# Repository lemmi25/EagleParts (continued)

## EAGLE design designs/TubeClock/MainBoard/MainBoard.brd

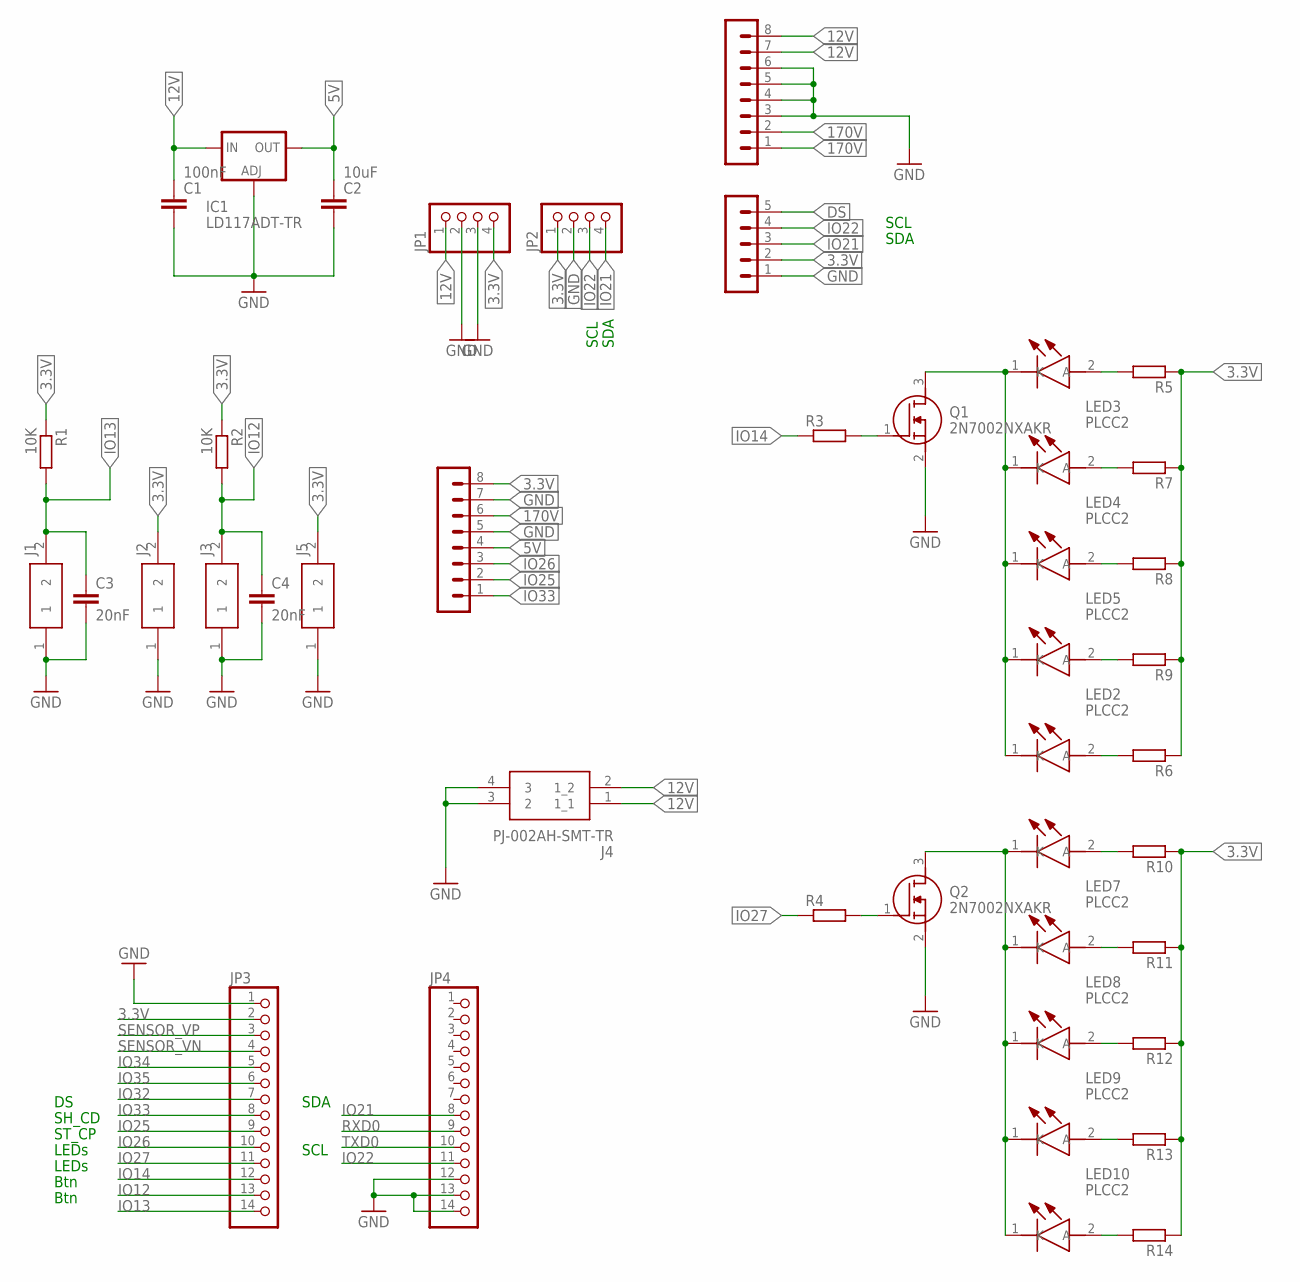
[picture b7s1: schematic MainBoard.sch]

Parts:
C1: 100nF; C1206
C2: 10uF; C1206
C3, C4: 20nF; C0805
IC1: LD117ADT-TR; DPACK
J1, J2, J3, J5: S2B-NSHSS-TB; SM02B-NSHSS-TB
J4: PJ-002AH-SMT-TR
JP1, JP2: PINHD-1X4; 1X04
JP3, JP4: PINHD-1X14; 1X14
LED1, LED2, LED3, LED4, LED5, LED6, LED7, LED8, LED9, LED10: PLCC2; LEDM3528X200N
Q1, Q2: 2N7002NXAKR; SOT95P230X110-3N
R1, R2: 10K; R1206
R3, R4, R5, R6, R7, R8, R9, R10, R11, R12, R13, R14: R-EU_1206R1206; R1206
SV1, SV7: PINHEADER-1X8; MA08-1
SV6: MA05-1

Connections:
3.3V: J2.2, J5.2, JP1.4, JP2.1, JP3.2, R1.1, R2.1, R5.1, R6.1, R7.1, R8.1, R9.1, R10.1, R11.1, R12.1, R13.1, R14.1, SV1.8, SV6.2
5V: C2.1, IC1.4 (OUT), SV1.4
12V: C1.1, IC1.3 (IN), J4.1 (1_1), J4.2 (1_2), JP1.1, SV7.7, SV7.8
170V: SV1.6, SV7.1, SV7.2
DS: SV6.5
GND: C1.2, C2.2, C3.2, C4.2, IC1.1 (ADJ), J1.1, J2.1, J3.1, J4.3 (2), J4.4 (3), J5.1, JP1.2, JP1.3, JP2.2, JP3.1, JP4.12, JP4.13, JP4.14, Q1.2 (S), Q2.2 (S), SV1.5, SV1.7, SV6.1, SV7.3, SV7.4, SV7.5, SV7.6
GND_LED_BTM: LED6.1 (K), LED7.1 (K), LED8.1 (K), LED9.1 (K), LED10.1 (K), Q2.3 (D)
GND_LED_TOP: LED1.1 (K), LED2.1 (K), LED3.1 (K), LED4.1 (K), LED5.1 (K), Q1.3 (D)
IO12: C4.1, J3.2, JP3.13, R2.2
IO13: C3.1, J1.2, JP3.14, R1.2
IO14: JP3.12, R3.1
IO21: JP2.4, JP4.8, SV6.3
IO22: JP2.3, JP4.11, SV6.4
IO25: JP3.9, SV1.2
IO26: JP3.10, SV1.3
IO27: JP3.11, R4.1
IO32: JP3.7
IO33: JP3.8, SV1.1
IO34: JP3.5
IO35: JP3.6
unnamed: Q1.1 (G), R3.2
unnamed: LED1.2 (A), R5.2
unnamed: LED3.2 (A), R7.2
unnamed: LED4.2 (A), R8.2
unnamed: LED5.2 (A), R9.2
unnamed: LED2.2 (A), R6.2
unnamed: Q2.1 (G), R4.2
unnamed: LED6.2 (A), R10.2
unnamed: LED7.2 (A), R11.2
unnamed: LED8.2 (A), R12.2
unnamed: LED9.2 (A), R13.2
unnamed: LED10.2 (A), R14.2
RXD0: JP4.9
SENSOR_VN: JP3.4
SENSOR_VP: JP3.3
TXD0: JP4.10

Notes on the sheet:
ST_CP
SH_CD
SCL
SDA
LEDs
Btn

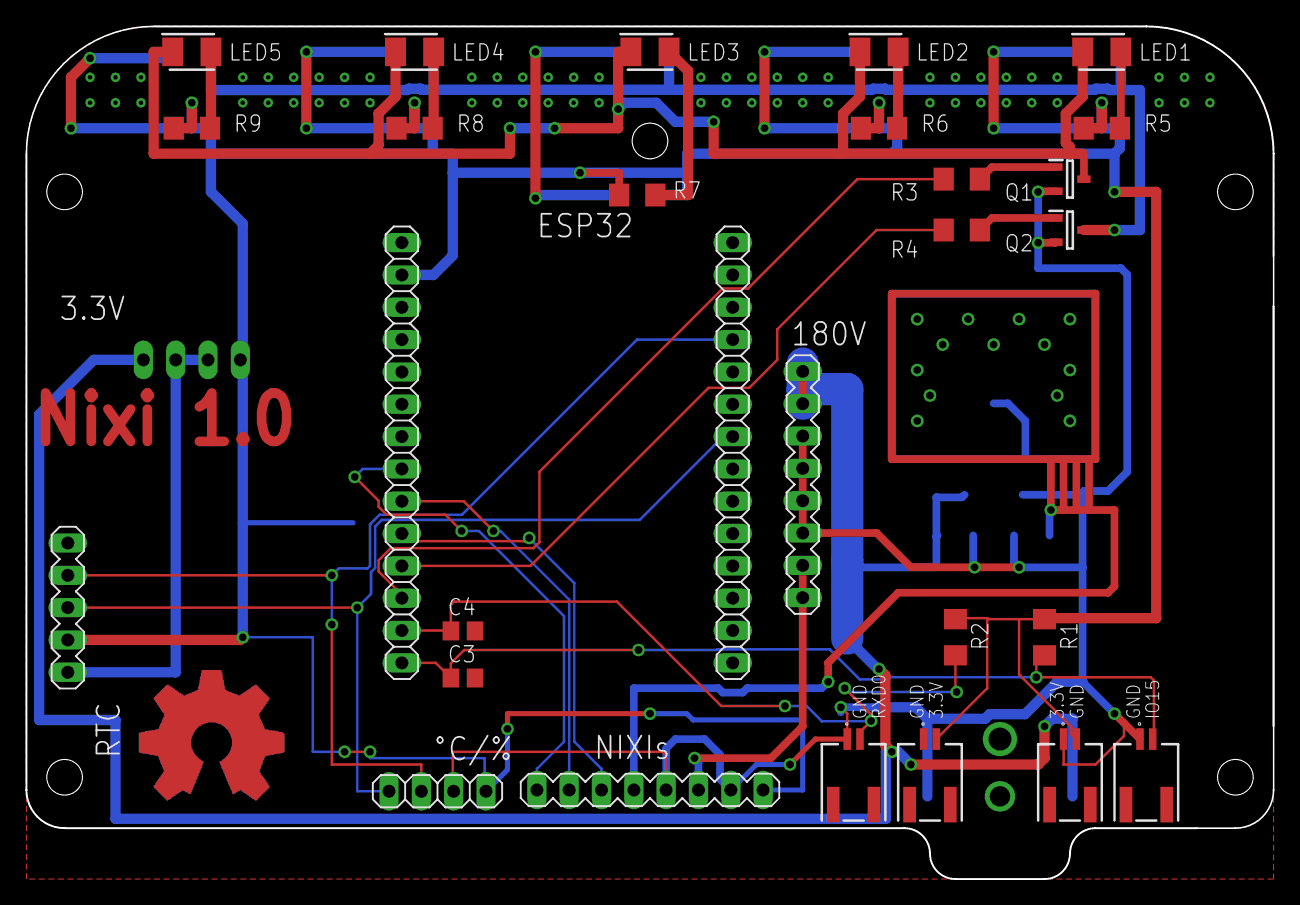
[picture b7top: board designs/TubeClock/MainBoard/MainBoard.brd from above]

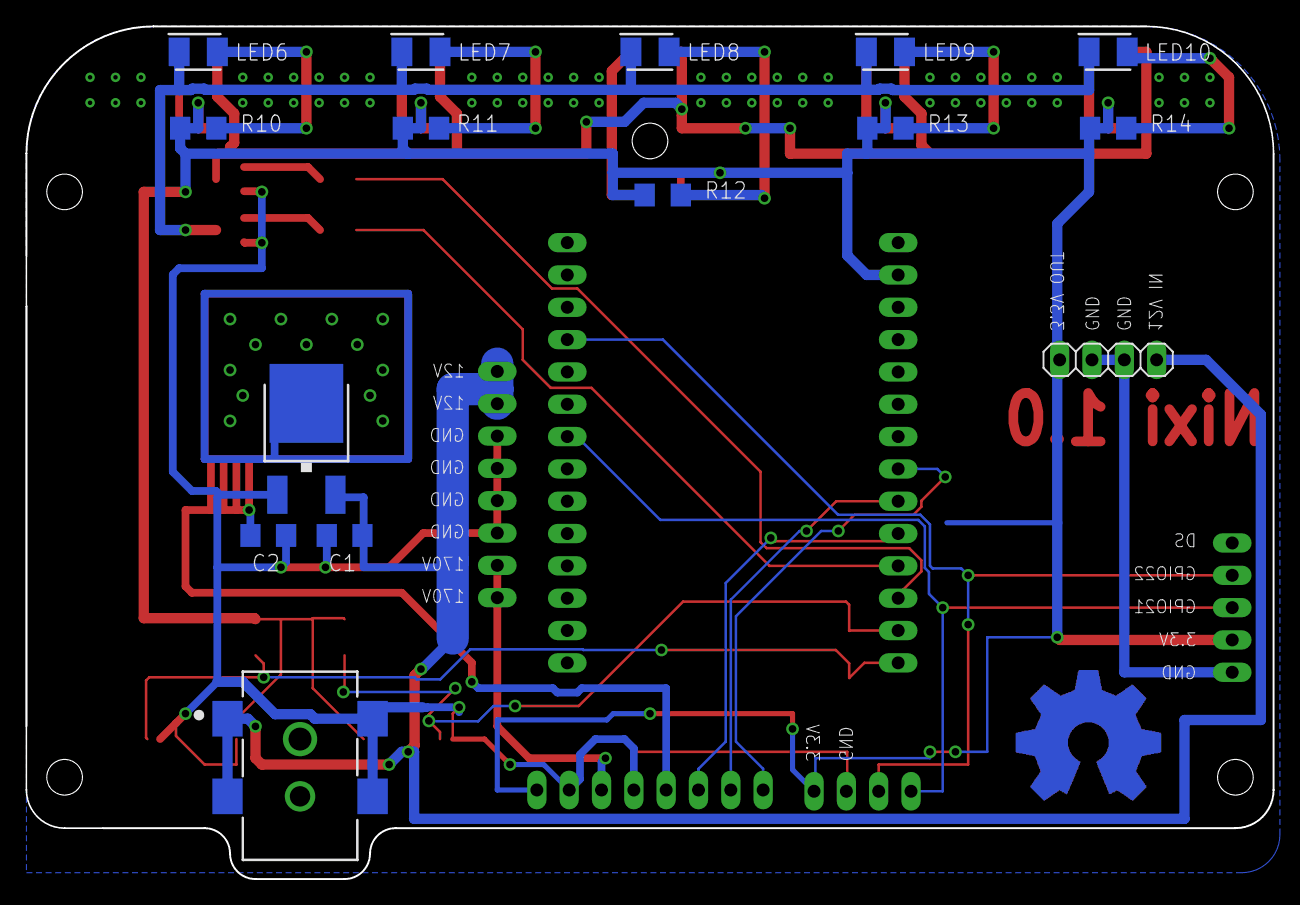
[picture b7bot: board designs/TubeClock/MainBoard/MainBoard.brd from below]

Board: 2 copper layers, 98.0 x 67.0 mm, 43 parts (15 on the bottom side), 28 nets.

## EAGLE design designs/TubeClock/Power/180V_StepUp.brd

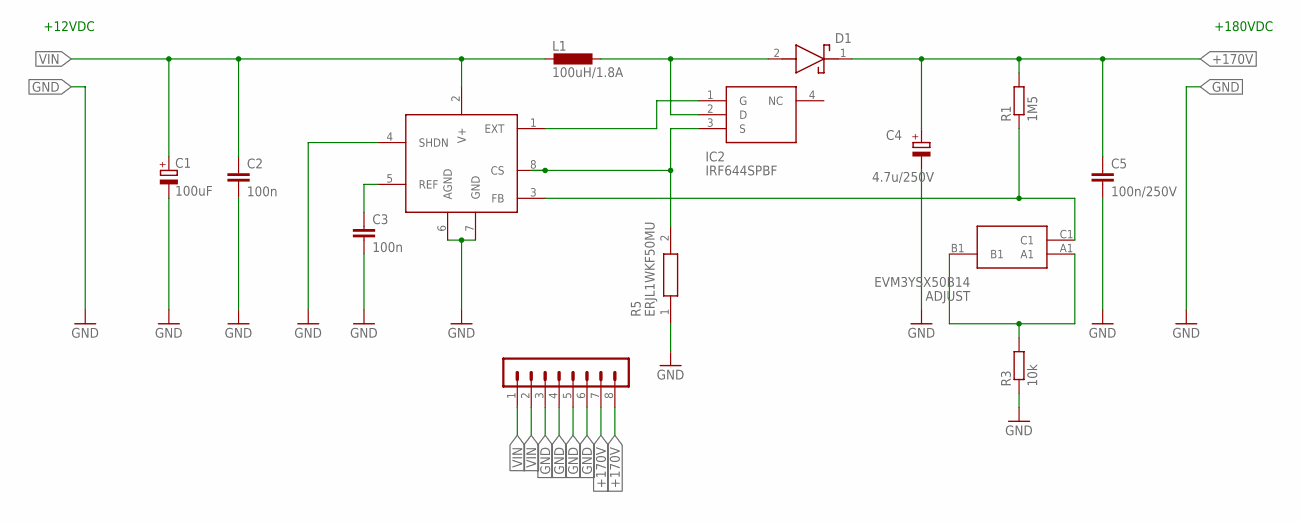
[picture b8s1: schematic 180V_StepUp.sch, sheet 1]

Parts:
ADJUST: EVM3YSX50B14
C1: 100uF; E2-4
C2, C3: 100n; C0805
C4: 4.7u/250V; E2,5-7
C5: 100n/250V; C2225K
D1: LSM115JE3_TR13; DIOM5436X330N
IC1: MAX1771; SO08
IC2: IRF644SPBF; TO254P1524X483-4N
L1: 100uH/1.8A; DO3316P
R1: 1M5; R0805
R3: 10k; R0805
R5: ERJL1WKF50MU; RESC6432X120N
SV1: PINHEADER-1X8; MA08-1

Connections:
+170V: C4.+, C5.1, D1.1 (K), R1.2, SV1.7, SV1.8
GND: C1.-, C2.2, C3.2, C4.-, C5.2, IC1.4 (SHDN), IC1.6 (AGND), IC1.7 (GND), R3.1, R5.1, SV1.3, SV1.4, SV1.5, SV1.6
unnamed: D1.2 (A), IC2.2 (D), L1.2
unnamed: C3.1, IC1.5 (REF)
unnamed: IC1.1 (EXT), IC2.1 (G)
unnamed: IC1.8 (CS), IC2.3 (S), R5.2
unnamed: ADJUST.C1, IC1.3 (FB), R1.1
unnamed: ADJUST.A1, ADJUST.B1, R3.2
VIN: C1.+, C2.1, IC1.2 (V+), L1.1, SV1.1, SV1.2

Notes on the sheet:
+12VDC
+180VDC

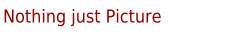
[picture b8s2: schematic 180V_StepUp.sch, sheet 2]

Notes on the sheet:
Nothing just Picture

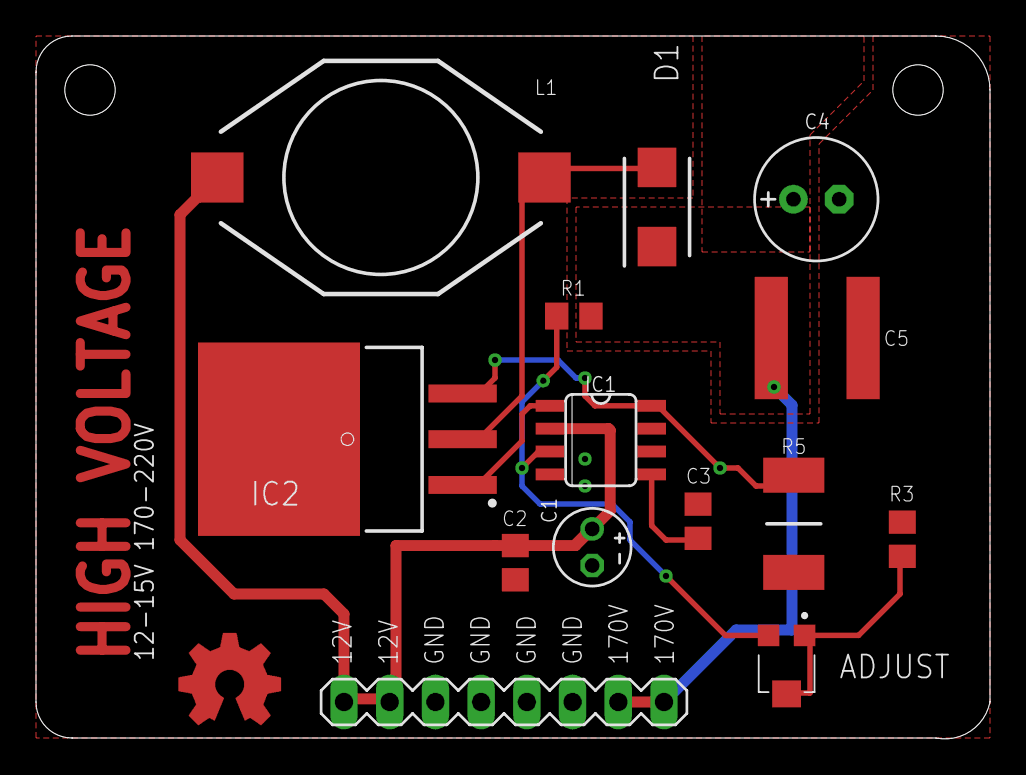
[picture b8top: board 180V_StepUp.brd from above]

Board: 2 copper layers, 53.0 x 39.0 mm, 14 parts (0 on the bottom side), 9 nets.

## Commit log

2019-09-21 added lbr form mouser parts and 3.3V Regulator design block
2019-09-21 added README
2019-09-23 updated README with partlist
2019-09-23 table cleaning in README
2019-09-23 added common parts to MAINSMD librarie and cad models
2019-09-23 added README info
2019-10-04 added 3.3V Dropdown converter
2019-10-04 added Visitenkarte
2019-10-04 updated sch and brd
2019-10-05 inductor change
2019-10-05 correct dimensions
2019-10-06 added ESP32 PCB
2019-10-12 added design block Logo
2019-10-12 added numitron sch and brd in a folder
2019-10-13 added designs Numitron modular first finish review tomorrow or tuesday
2019-10-14 added lbr common pin header
2019-10-14 added correct measurements
2019-10-15 finished mainboard
2019-10-16 added last design tunes
2019-10-22 added correct image for Geansefett for 3.3V Converter
2019-11-04 added nixi tube library
2019-11-09 added ESP32 Capacitor values
2019-11-09 corrected ESP32 on/off error
2019-11-09 corrected 3.3V gnd v font
2019-11-10 changed 1206 100uF Capacitor
2019-11-10 numitron 4 resistor error correction
2019-11-24 added changes
2019-11-25 corrected numitron pcb
2019-12-01 added nixi tube project
2019-12-01 added details for nixitube
2019-12-01 pushed to fusion
2019-12-01 added parts for nixi clock final check during the week
2019-12-03 changed ESP32 on/off switch distance to pins
2020-01-10 added step up converter Vin 12-15 Vout 150-220
2020-01-12 added new nixi clock design top board
2020-01-14 started work on mainboard
2020-01-15 added pinout on mainboard
2020-01-16 added work to mainboard LEDs N-Channel Mosfet and names tNames
2020-01-16 further work on mainboard
2020-01-18 added nixiClock brd and sheet with new design OSH
2020-01-19 integrated T/H sensor
2020-01-20 added new cam data and made last checks before order :o
2020-01-26 started cheap 555 Nixi Power supply
2020-02-03 added first IN-4 Design and edited mainboard to fit all screws for IN-4
2020-02-04 improved design of IN-4
2020-02-06 added new design in brd from NI-4
2020-02-07 improved design of mainboard by edding a buzzer
2020-02-11 worked on routing in IN4
2020-02-15 worked on brd layout NI-4
2020-02-17 final review of design and ordered from JLC PCB
2020-02-24 added DA-2000 pcb sch and brd with autorouter
2020-03-08 fixed errors in mainboard and 180V 555 Step up Converter
2020-04-10 modified nixi proj. and added EasterRadio project
2020-04-10 added EasterRadio parts to MouserUseful LBR
2020-04-11 added ESP32 design block
2020-04-11 added design block for lepo charger
2020-04-11 finished PAM8403 schematic
2020-04-11 Working Progress for Si4844 radio ic
2020-04-12 changed 2k to Data Sheet value (depence on battery that is to be charged)
2020-04-12 added potentiometer
2020-04-12 added design rules and info for tools of CNC
2020-04-12 added charging ic and radio fm/am chip
2020-04-13 added pins for different sheet connections
2020-04-13 added p-channel mosfet
2020-04-13 added load to battery in Lipo Charger IC
2020-04-13 removed 12V to 5V voltage regulator and added singel sch and brd for power
2020-04-13 added design rules for CNC
2020-04-13 changed to correct diode and designed power pcb
2020-04-16 Corrected Mistakes in Schematics
2020-04-26 added cam for power easter radio
2020-05-03 added numitrons for tube clock
2020-05-05 added schematic and parts for RS232 to CAN
2020-05-05 finished schematic for RS232 to CAN
2020-05-09 changed polarity of power and battery + drain source change imn p channel mosfet
2020-05-09 Started amplifier wiring
2020-05-10 added bottom case CNC file
2020-05-10 added bottom case CNC file new tool offset
2020-05-13 brd amplifier almost finished
2020-05-13 added ESP32 brd and sch + gerber
2020-05-13 finalized amplifier board
2020-05-16 Added radio chip brd file
2020-05-16 added gcode files for CNC
2020-06-11 added RTC
2020-06-12 updated RTC BRD
2020-06-12 finished RTC Brd
2020-06-14 added brd laxout
2020-06-14 changed ESP32 board for correct on off switch
2020-06-15 DA2000 Update
2020-07-05 changed radio IC
2020-07-05 added gcode for radio chip
2020-11-08 changed power board: added comments in schematic and added new LED (to be checked) which is on as soon as charging is done
2020-11-09 added battery loader + 3.3V regulator
2020-11-09 Added comments to radioIC.sch
2020-11-12 added amplifier with stereo jack
2020-11-14 added amplifier brd
2020-11-15 added final power and amplifier design and ESP32 E footprint
2020-11-18 added ESP32 wrover E schematic
2020-11-19 added STM32 CAN to RS232 Adapter
2020-11-22 ESP32 brd layout
2020-11-24 added brd layout for RS232 to can
2020-11-28 added Poti and Encoder pcb
2020-11-28 cleaned up libraries
2020-11-28 everything pushed to fusion
2020-12-03 added esd for rs232 to can
2020-12-06 added mainboard layout and new 3.5mm jack
2020-12-07 added more stuff to pcb main for radio
2020-12-09 started board routing
2020-12-13 finalzed brd layout main pcb
2020-12-14 Moved one wire a bit
2020-12-14 Moved Drilled hole a bit
2020-12-14 removed crlf ending amplifier brd
2020-12-14 final changes on mainboard
2020-12-14 final changes ready for purchase
2021-01-06 changed poti and encoder pcb to correct schematic and brd + mainboard change for push btn on rotary encoder
2021-01-17 changes for new design excluding swap for amplifier
2021-01-17 changes for new design including swap for amplifier
2021-01-25 small changes to easter radio mainboard started for in14 nixi tubes and cleanup
2021-01-30 last commit before change to new mainboard of tube clock
2021-02-02 changed mainboard design radio
2021-02-02 added new mainboard design
2021-02-03 added changes to mainboard for speaker
2021-02-03 small change for mounting hole of power on mainboard
2021-03-15 added new design of radio parts added 3.3V mark
2021-03-24 added new design of radio parts slide change naming on mainboard and routing on radio ic
2021-03-30 Fixed encoder issue: Terminal C connected to 3.3V instead of GND which is in contrast to the datasheet circuit diagram but is working.
2021-04-01 added final revisions to amplifier power radio ic and control pcbs
2021-04-02 checked Mainboard and esp32
2021-04-03 small change to flsh chip for esp32
2021-04-03 minor changes to ESP32 values of resistor and capacitor
2021-04-05 added docs
2021-04-05 Update Makefile
2021-04-05 added ordering files
2021-04-05 removed docs from ordering apr 21 branch
2021-04-05 added build folder with index.html
2021-04-08 added new files for docu to git
2021-04-08 new structure for docu
2021-04-08 deleted docsrc folder
2021-04-08 Trigger rebuild
2021-04-09 added index.html to docs
2021-04-09 added first wiki entry for MainBoard
2021-04-25 minor changes
2021-05-06 few changes
2021-05-22 little changes
